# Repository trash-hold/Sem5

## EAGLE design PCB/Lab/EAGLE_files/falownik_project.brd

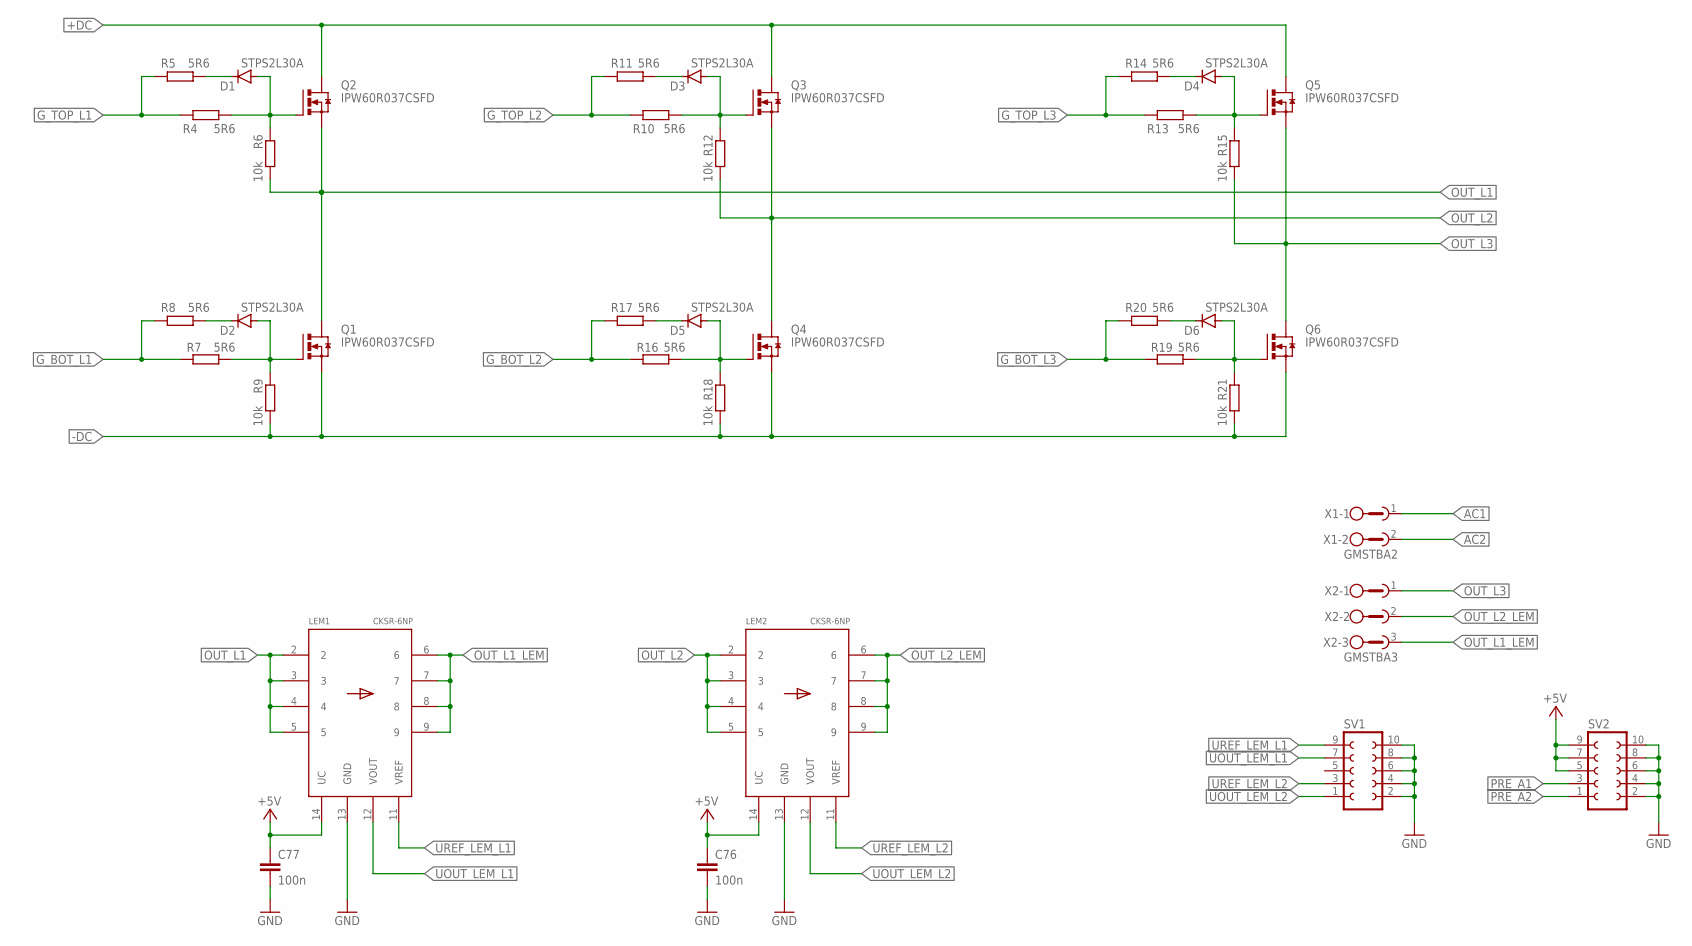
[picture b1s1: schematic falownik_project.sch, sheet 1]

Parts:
C76, C77: 100n; C0805
D1, D2, D3, D4, D5, D6: STPS2L30A; DO214AC
LEM1, LEM2: CKSR-6NP; CKSR
Q1, Q2, Q3, Q4, Q5, Q6: IPW60R037CSFD; TO247BV
R4, R5, R7, R8, R10, R11, R13, R14, R16, R17, R19, R20: 5R6; R0603
R6, R9, R12, R15, R18, R21: 10k; R0603
SV1, SV2: FE05-2
X1: GMSTBA2
X2: GMSTBA3

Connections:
+5V: C76.1, C77.1, LEM1.14 (UC), LEM2.14 (UC), SV2.5, SV2.7, SV2.9; also elsewhere on the board
+DC: Q2.D, Q3.D, Q5.D; also elsewhere on the board
-DC: Q1.S, Q4.S, Q6.S, R9.2, R18.2, R21.2; also elsewhere on the board
AC1: X1.1; also elsewhere on the board
AC2: X1.2; also elsewhere on the board
GND: C76.2, C77.2, LEM1.13 (GND), LEM2.13 (GND), SV1.2, SV1.4, SV1.6, SV1.8, SV1.10, SV2.2, SV2.4, SV2.6, SV2.8, SV2.10; also elsewhere on the board
G_BOT_L1: R7.1, R8.1; also elsewhere on the board
G_BOT_L2: R16.1, R17.1; also elsewhere on the board
G_BOT_L3: R19.1, R20.1; also elsewhere on the board
G_TOP_L1: R4.1, R5.1; also elsewhere on the board
G_TOP_L2: R10.1, R11.1; also elsewhere on the board
G_TOP_L3: R13.1, R14.1; also elsewhere on the board
unnamed: D1.A, Q2.G, R4.2, R6.1
unnamed: D1.C, R5.2
unnamed: D2.A, Q1.G, R7.2, R9.1
unnamed: D2.C, R8.2
unnamed: D3.A, Q3.G, R10.2, R12.1
unnamed: D3.C, R11.2
unnamed: D4.A, Q5.G, R13.2, R15.1
unnamed: D4.C, R14.2
unnamed: D5.A, Q4.G, R16.2, R18.1
unnamed: D5.C, R17.2
unnamed: D6.A, Q6.G, R19.2, R21.1
unnamed: D6.C, R20.2
OUT_L1: LEM1.2, LEM1.3, LEM1.4, LEM1.5, Q1.D, Q2.S, R6.2; also elsewhere on the board
OUT_L1_LEM: LEM1.6, LEM1.7, LEM1.8, LEM1.9, X2.3
OUT_L2: LEM2.2, LEM2.3, LEM2.4, LEM2.5, Q3.S, Q4.D, R12.2; also elsewhere on the board
OUT_L2_LEM: LEM2.6, LEM2.7, LEM2.8, LEM2.9, X2.2
OUT_L3: Q5.S, Q6.D, R15.2, X2.1; also elsewhere on the board
PRE_A1: SV2.3; also elsewhere on the board
PRE_A2: SV2.1; also elsewhere on the board
UOUT_LEM_L1: LEM1.12 (VOUT), SV1.7
UOUT_LEM_L2: LEM2.12 (VOUT), SV1.1
UREF_LEM_L1: LEM1.11 (VREF), SV1.9
UREF_LEM_L2: LEM2.11 (VREF), SV1.3

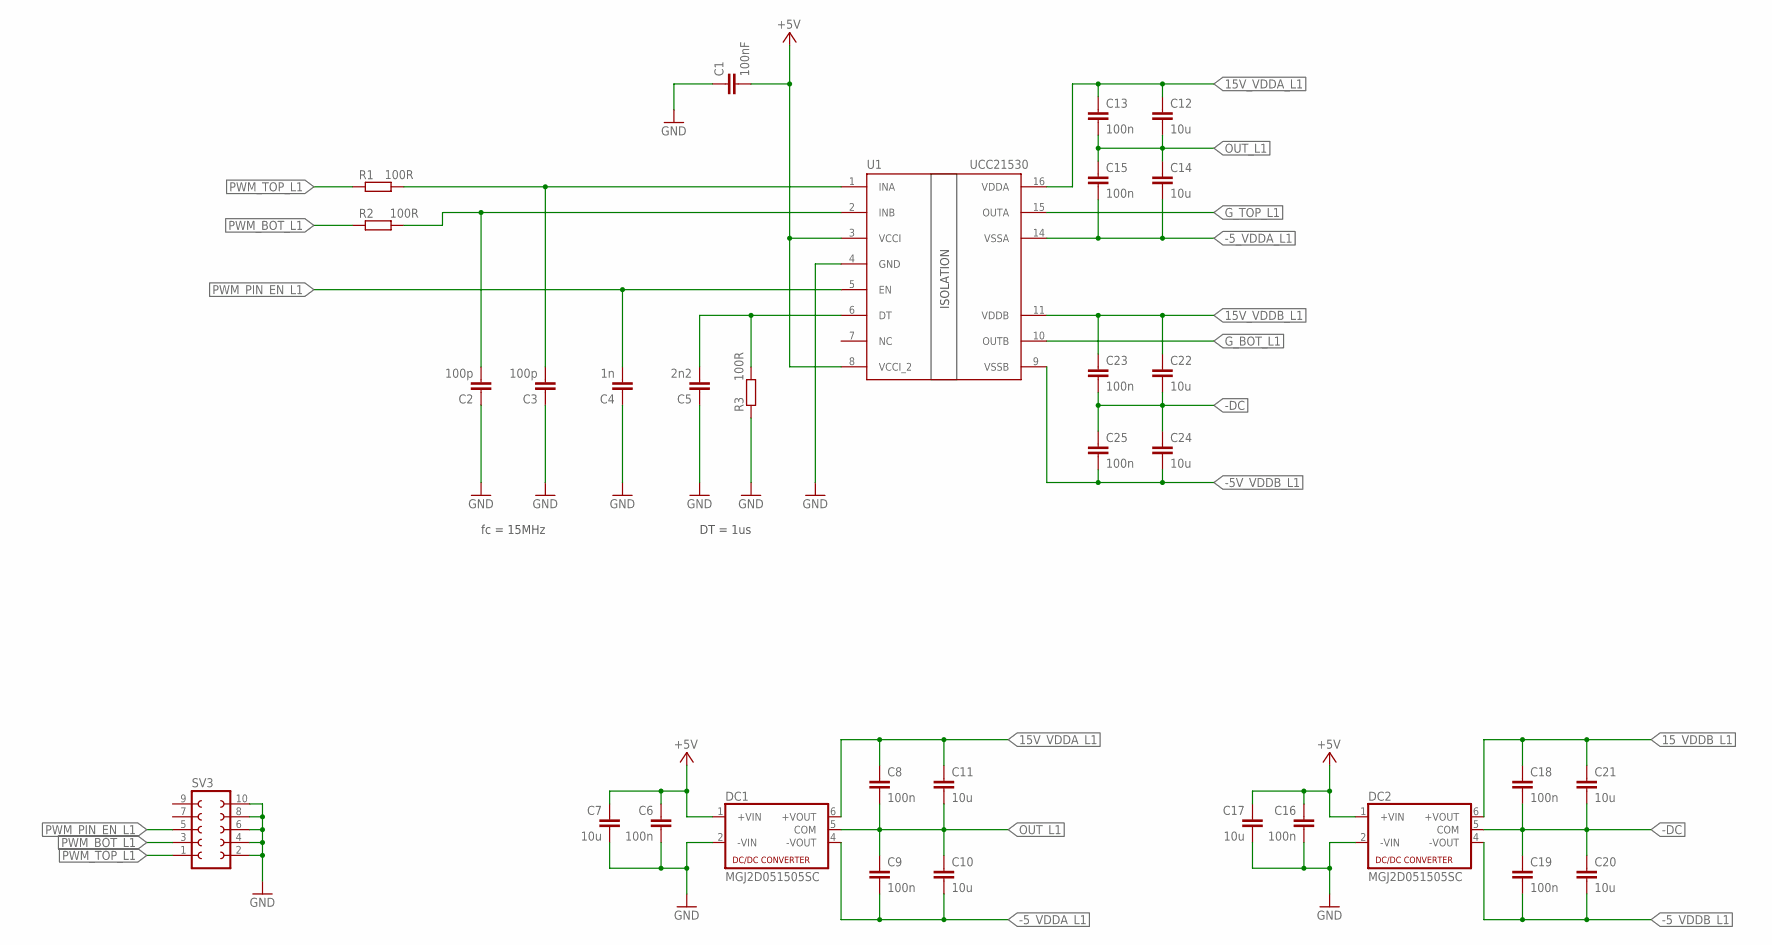
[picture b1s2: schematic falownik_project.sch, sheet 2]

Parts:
C1: 100nF; C0603
C2, C3: 100p; C0603
C4: 1n; C0603
C5: 2n2; C0603
C6, C8, C9, C13, C15, C16, C18, C19, C23, C25: 100n; C0603
C7, C10, C14, C17, C20, C24: 10u; C1206
C11, C12, C21, C22: 10u; C1210
DC1, DC2: MGJ2D051505SC
R1, R2, R3: 100R; R0603
SV3: FE05-2
U1: UCC21530; SOIC-14

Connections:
15V_VDDA_L1: C8.1, C11.1, DC1.6 (+VOUT)
15_VDDB_L1: C18.1, C21.1, DC2.6 (+VOUT)
+5V: C1.2, C6.1, C7.1, C16.1, C17.1, DC1.1 (+VIN), DC2.1 (+VIN), U1.3 (VCCI), U1.8 (VCCI_2); also elsewhere on the board
-5_VDDA_L1: C9.2, C10.2, DC1.4 (-VOUT)
-5_VDDB_L1: C19.2, C20.2, DC2.4 (-VOUT)
-DC: C18.2, C19.1, C20.1, C21.2, C22.2, C23.2, C24.1, C25.1, DC2.5 (COM); also elsewhere on the board
GND: C1.1, C2.1, C3.1, C4.1, C5.1, C6.2, C7.2, C16.2, C17.2, DC1.2 (-VIN), DC2.2 (-VIN), R3.1, SV3.2, SV3.4, SV3.6, SV3.8, SV3.10, U1.4 (GND); also elsewhere on the board
G_BOT_L1: U1.10 (OUTB); also elsewhere on the board
G_TOP_L1: U1.15 (OUTA); also elsewhere on the board
unnamed: C3.2, R1.2, U1.1 (INA)
unnamed: C2.2, R2.2, U1.2 (INB)
unnamed: C5.2, R3.2, U1.6 (DT)
unnamed: C14.2, C15.2, U1.14 (VSSA)
unnamed: C12.1, C13.1, U1.16 (VDDA)
unnamed: C24.2, C25.2, U1.9 (VSSB)
unnamed: C22.1, C23.1, U1.11 (VDDB)
OUT_L1: C8.2, C9.1, C10.1, C11.2, C12.2, C13.2, C14.1, C15.1, DC1.5 (COM); also elsewhere on the board
PWM_BOT_L1: R2.1, SV3.3
PWM_PIN_EN_L1: C4.2, SV3.5, U1.5 (EN)
PWM_TOP_L1: R1.1, SV3.1

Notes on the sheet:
DT = 1us
fc = 15MHz

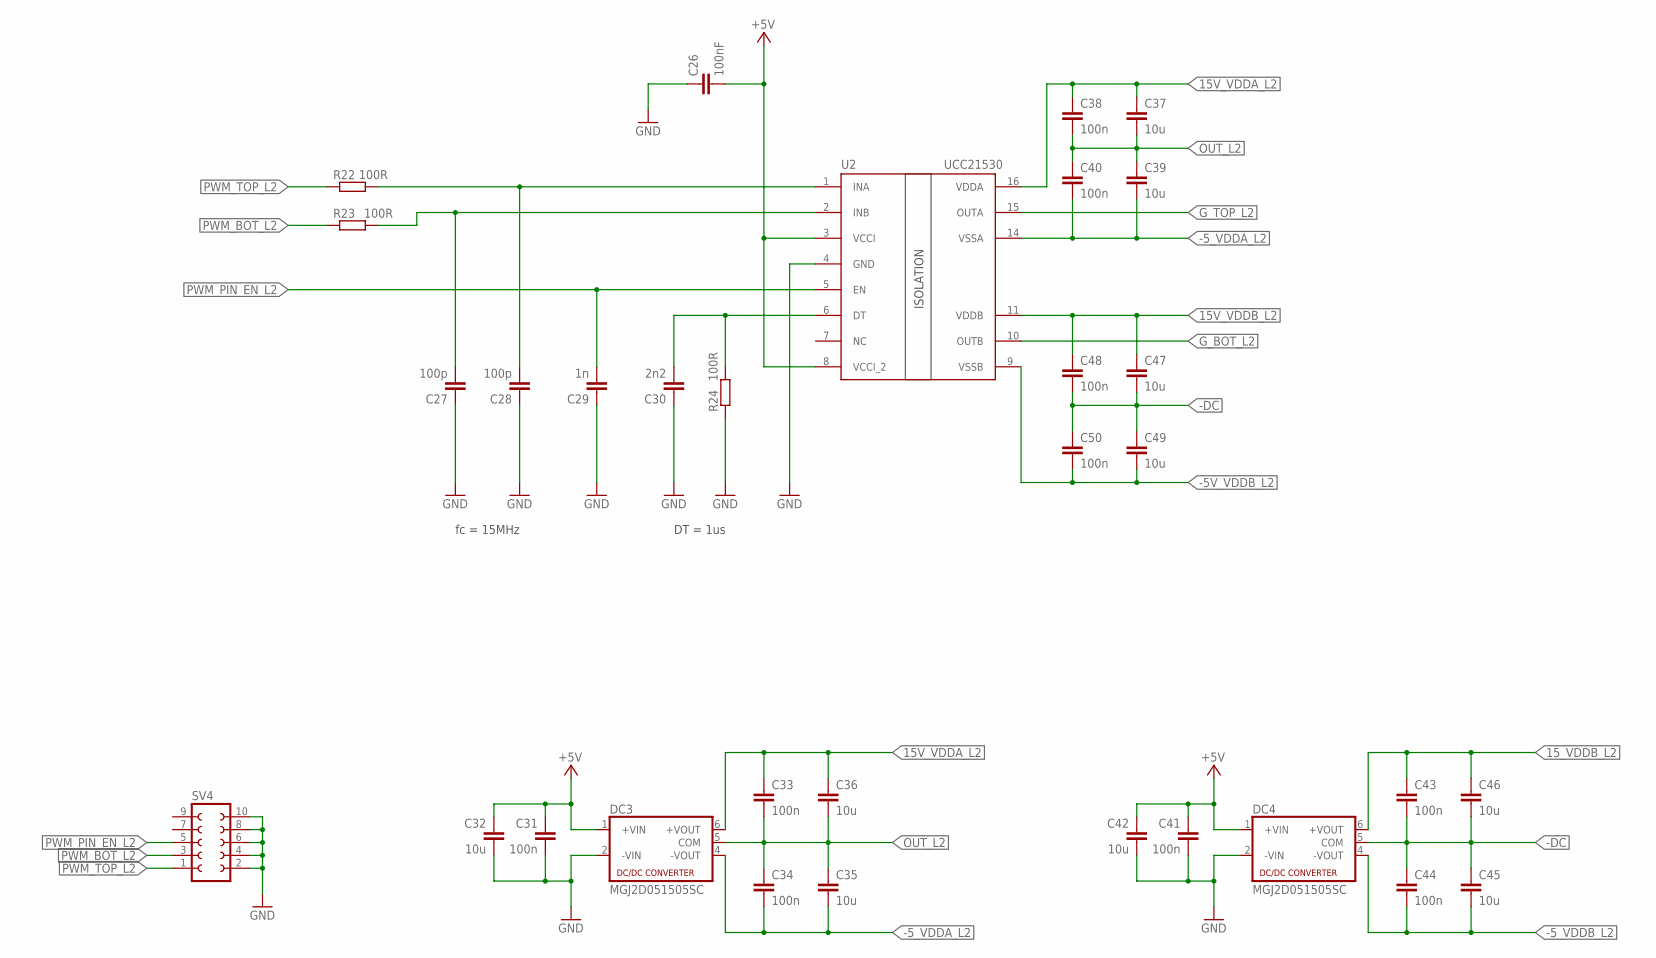
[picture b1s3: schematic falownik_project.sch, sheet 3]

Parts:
C26: 100nF; C0603
C27, C28: 100p; C0603
C29: 1n; C0603
C30: 2n2; C0603
C31, C33, C34, C38, C40, C41, C43, C44, C48, C50: 100n; C0603
C32, C35, C39, C42, C45, C49: 10u; C1206
C36, C37, C46, C47: 10u; C1210
DC3, DC4: MGJ2D051505SC
R22, R23, R24: 100R; R0603
SV4: FE05-2
U2: UCC21530; SOIC-14

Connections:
15V_VDDA_L2: C33.1, C36.1, DC3.6 (+VOUT)
15_VDDB_L2: C43.1, C46.1, DC4.6 (+VOUT)
+5V: C26.2, C31.1, C32.1, C41.1, C42.1, DC3.1 (+VIN), DC4.1 (+VIN), U2.3 (VCCI), U2.8 (VCCI_2); also elsewhere on the board
-5_VDDA_L2: C34.2, C35.2, DC3.4 (-VOUT)
-5_VDDB_L2: C44.2, C45.2, DC4.4 (-VOUT)
-DC: C43.2, C44.1, C45.1, C46.2, C47.2, C48.2, C49.1, C50.1, DC4.5 (COM); also elsewhere on the board
GND: C26.1, C27.1, C28.1, C29.1, C30.1, C31.2, C32.2, C41.2, C42.2, DC3.2 (-VIN), DC4.2 (-VIN), R24.1, SV4.2, SV4.4, SV4.6, SV4.8, SV4.10, U2.4 (GND); also elsewhere on the board
G_BOT_L2: U2.10 (OUTB); also elsewhere on the board
G_TOP_L2: U2.15 (OUTA); also elsewhere on the board
unnamed: C28.2, R22.2, U2.1 (INA)
unnamed: C27.2, R23.2, U2.2 (INB)
unnamed: C30.2, R24.2, U2.6 (DT)
unnamed: C39.2, C40.2, U2.14 (VSSA)
unnamed: C37.1, C38.1, U2.16 (VDDA)
unnamed: C49.2, C50.2, U2.9 (VSSB)
unnamed: C47.1, C48.1, U2.11 (VDDB)
OUT_L2: C33.2, C34.1, C35.1, C36.2, C37.2, C38.2, C39.1, C40.1, DC3.5 (COM); also elsewhere on the board
PWM_BOT_L2: R23.1, SV4.3
PWM_PIN_EN_L2: C29.2, SV4.5, U2.5 (EN)
PWM_TOP_L2: R22.1, SV4.1

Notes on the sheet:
DT = 1us
fc = 15MHz

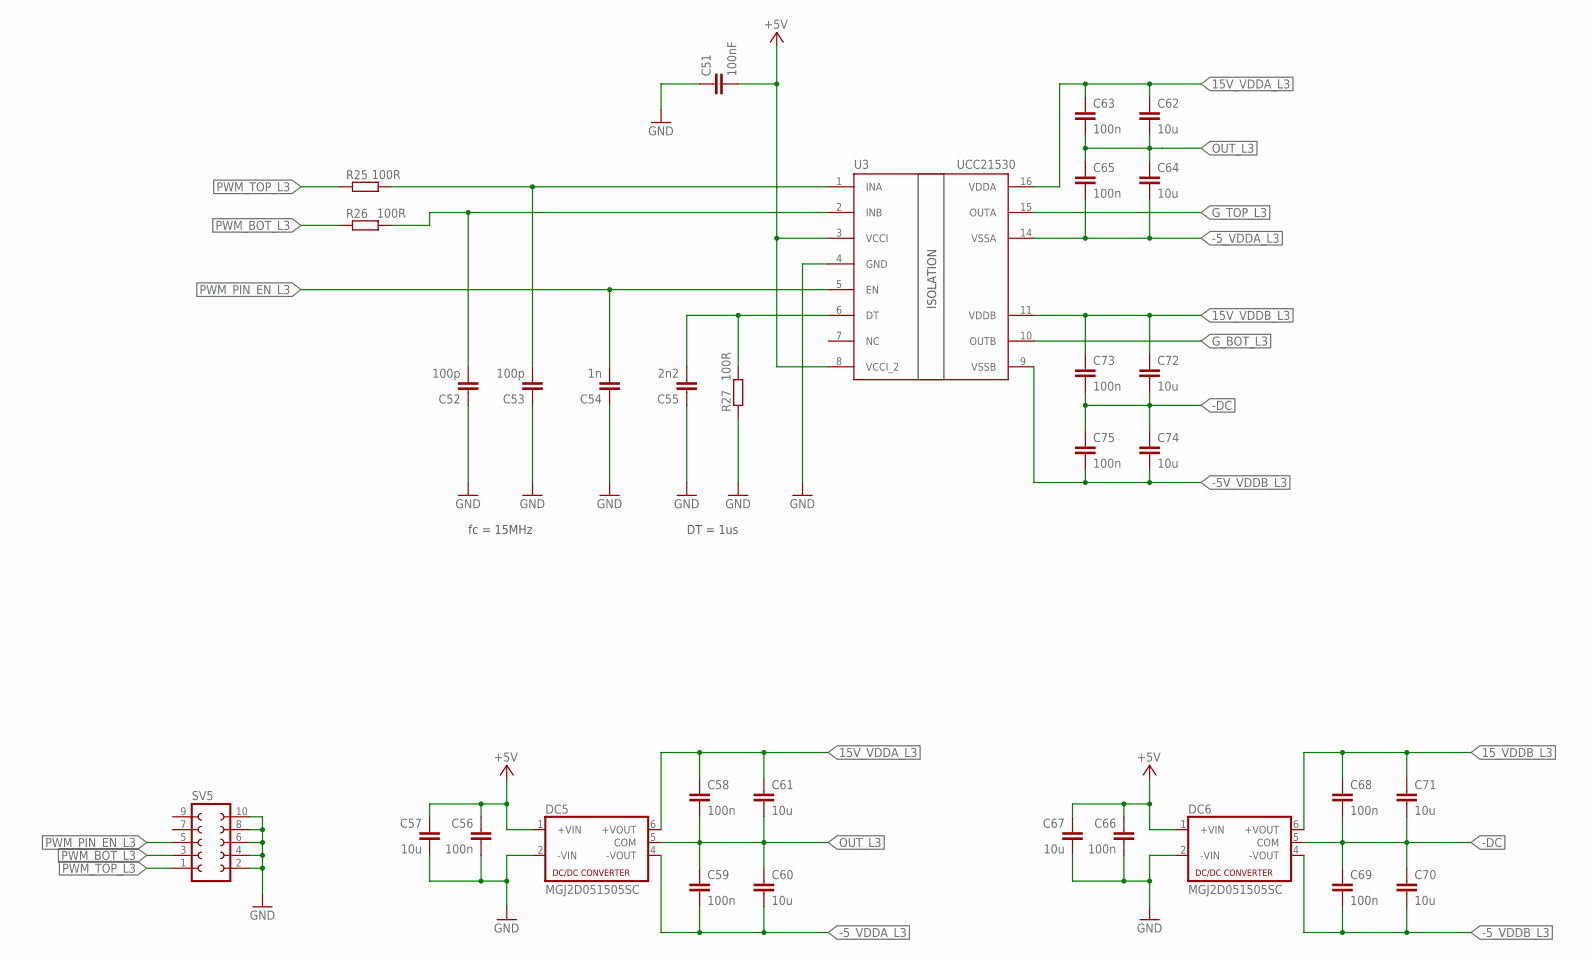
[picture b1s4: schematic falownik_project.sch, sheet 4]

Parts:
C51: 100nF; C0603
C52, C53: 100p; C0603
C54: 1n; C0603
C55: 2n2; C0603
C56, C58, C59, C63, C65, C66, C68, C69, C73, C75: 100n; C0603
C57, C60, C64, C67, C70, C74: 10u; C1206
C61, C62, C71, C72: 10u; C1210
DC5, DC6: MGJ2D051505SC
R25, R26, R27: 100R; R0603
SV5: FE05-2
U3: UCC21530; SOIC-14

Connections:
15V_VDDA_L3: C58.1, C61.1, DC5.6 (+VOUT)
15_VDDB_L3: C68.1, C71.1, DC6.6 (+VOUT)
+5V: C51.2, C56.1, C57.1, C66.1, C67.1, DC5.1 (+VIN), DC6.1 (+VIN), U3.3 (VCCI), U3.8 (VCCI_2); also elsewhere on the board
-5_VDDA_L3: C59.2, C60.2, DC5.4 (-VOUT)
-5_VDDB_L3: C69.2, C70.2, DC6.4 (-VOUT)
-DC: C68.2, C69.1, C70.1, C71.2, C72.2, C73.2, C74.1, C75.1, DC6.5 (COM); also elsewhere on the board
GND: C51.1, C52.1, C53.1, C54.1, C55.1, C56.2, C57.2, C66.2, C67.2, DC5.2 (-VIN), DC6.2 (-VIN), R27.1, SV5.2, SV5.4, SV5.6, SV5.8, SV5.10, U3.4 (GND); also elsewhere on the board
G_BOT_L3: U3.10 (OUTB); also elsewhere on the board
G_TOP_L3: U3.15 (OUTA); also elsewhere on the board
unnamed: C53.2, R25.2, U3.1 (INA)
unnamed: C52.2, R26.2, U3.2 (INB)
unnamed: C55.2, R27.2, U3.6 (DT)
unnamed: C64.2, C65.2, U3.14 (VSSA)
unnamed: C62.1, C63.1, U3.16 (VDDA)
unnamed: C74.2, C75.2, U3.9 (VSSB)
unnamed: C72.1, C73.1, U3.11 (VDDB)
OUT_L3: C58.2, C59.1, C60.1, C61.2, C62.2, C63.2, C64.1, C65.1, DC5.5 (COM); also elsewhere on the board
PWM_BOT_L3: R26.1, SV5.3
PWM_PIN_EN_L3: C54.2, SV5.5, U3.5 (EN)
PWM_TOP_L3: R25.1, SV5.1

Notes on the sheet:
DT = 1us
fc = 15MHz

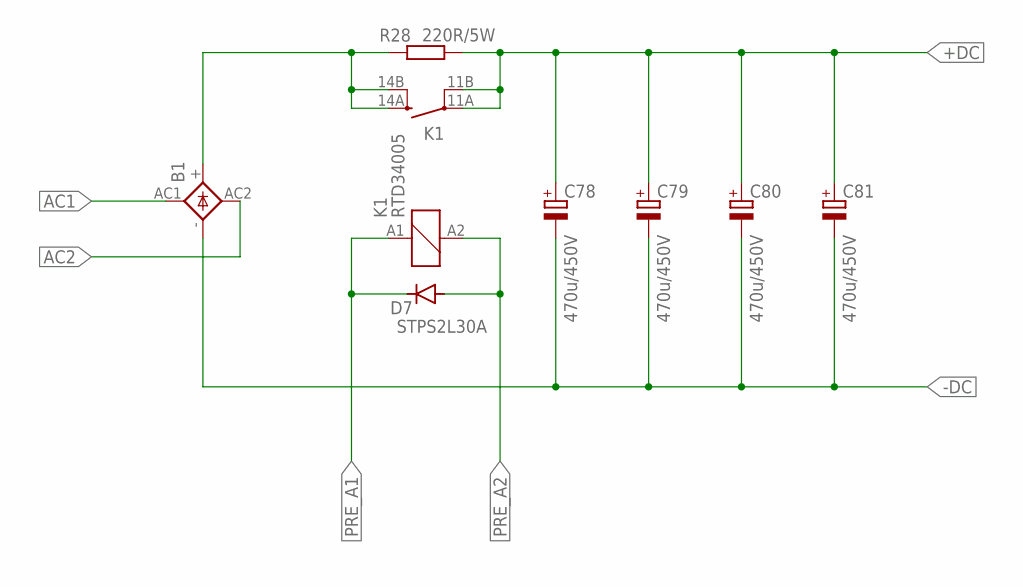
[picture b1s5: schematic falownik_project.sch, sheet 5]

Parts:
B1: GBPC80X
C78, C79, C80, C81: 470u/450V; EB30D
D7: STPS2L30A; DO214AC
K1: RTD34005; RT-N/O16A5
R28: 220R/5W; VTA52

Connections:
+DC: C78.+, C79.+, C80.+, C81.+, K1.11A (PA), K1.11B (PB), R28.2; also elsewhere on the board
-DC: B1.-, C78.-, C79.-, C80.-, C81.-; also elsewhere on the board
AC1: B1.AC1; also elsewhere on the board
AC2: B1.AC2; also elsewhere on the board
unnamed: B1.+, K1.14A (SA), K1.14B (SB), R28.1
PRE_A1: D7.C, K1.A1 (1); also elsewhere on the board
PRE_A2: D7.A, K1.A2 (2); also elsewhere on the board

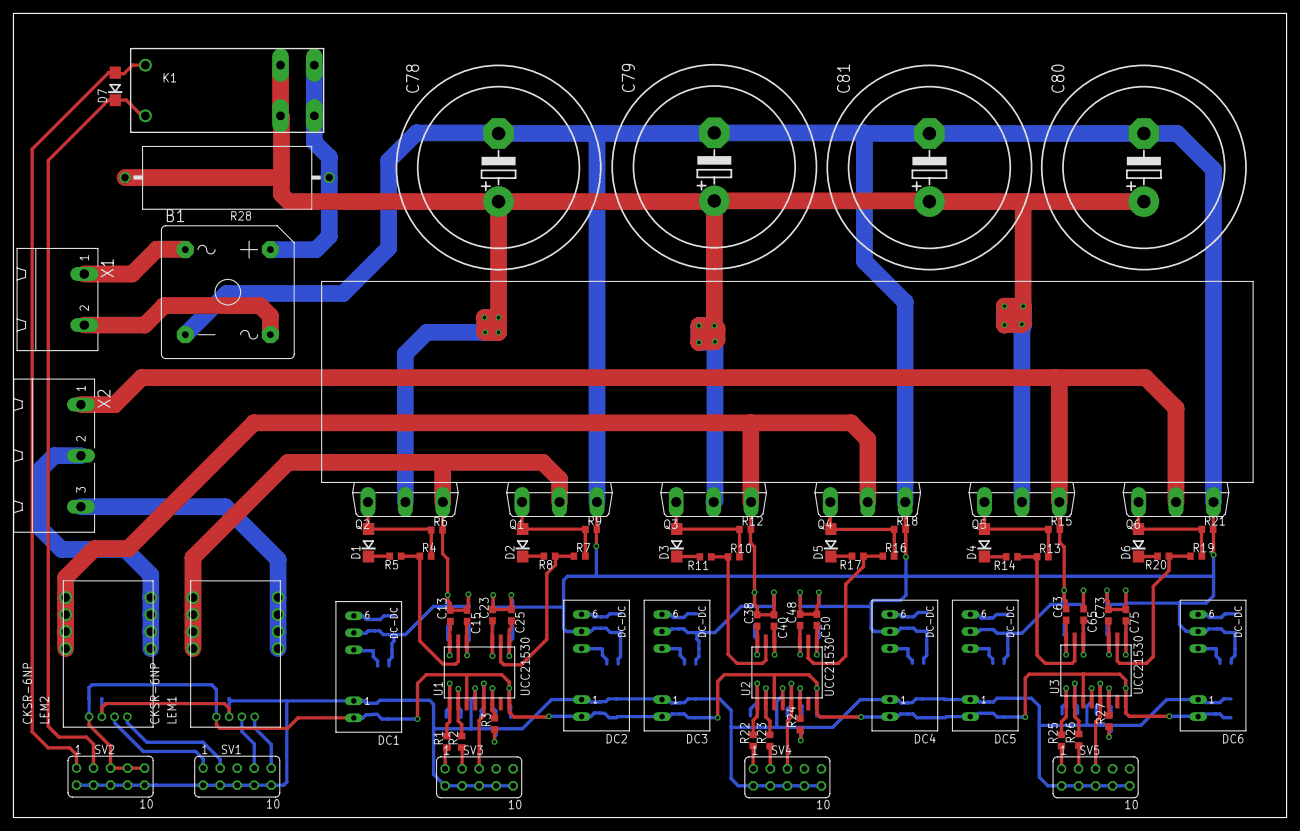
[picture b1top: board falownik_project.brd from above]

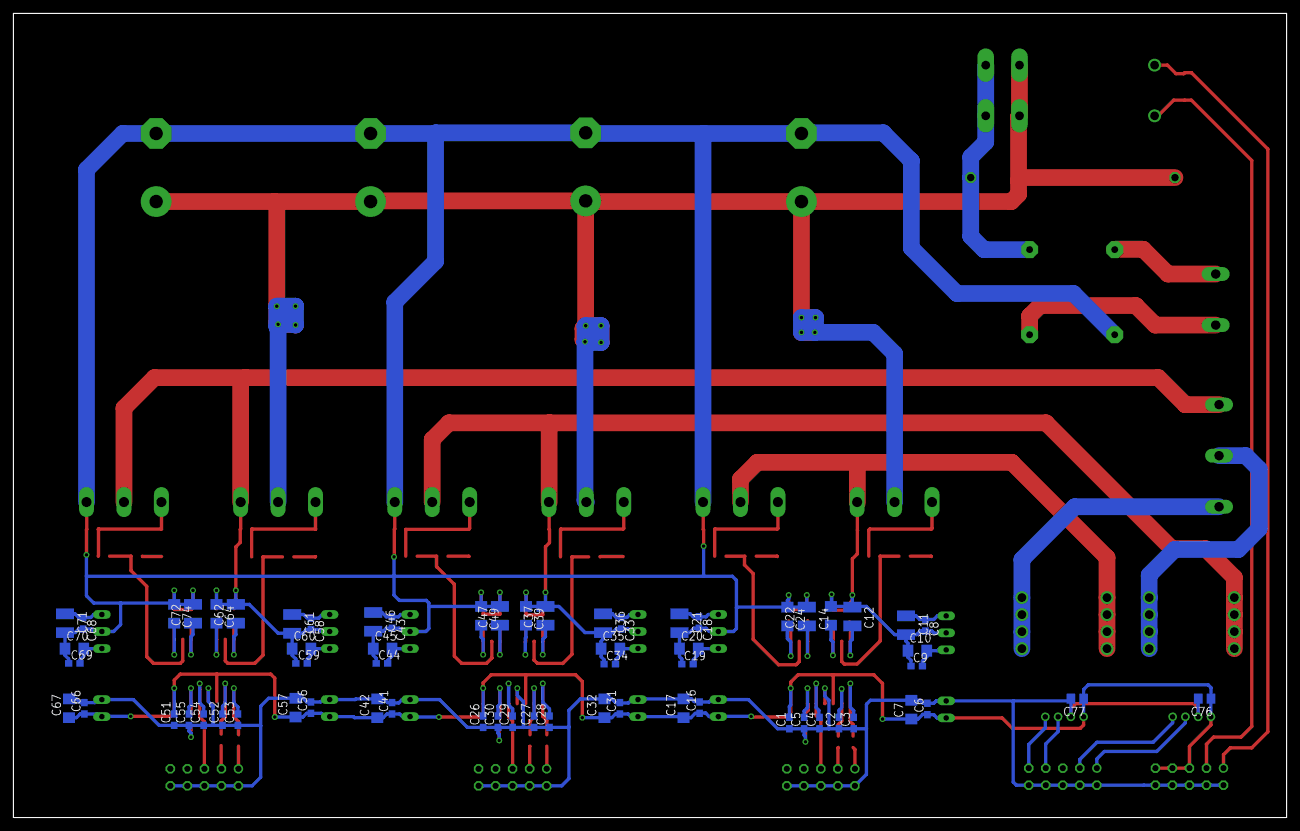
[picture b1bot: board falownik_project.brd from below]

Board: 2 copper layers, 190.0 x 120.0 mm, 142 parts (65 on the bottom side), 78 nets.

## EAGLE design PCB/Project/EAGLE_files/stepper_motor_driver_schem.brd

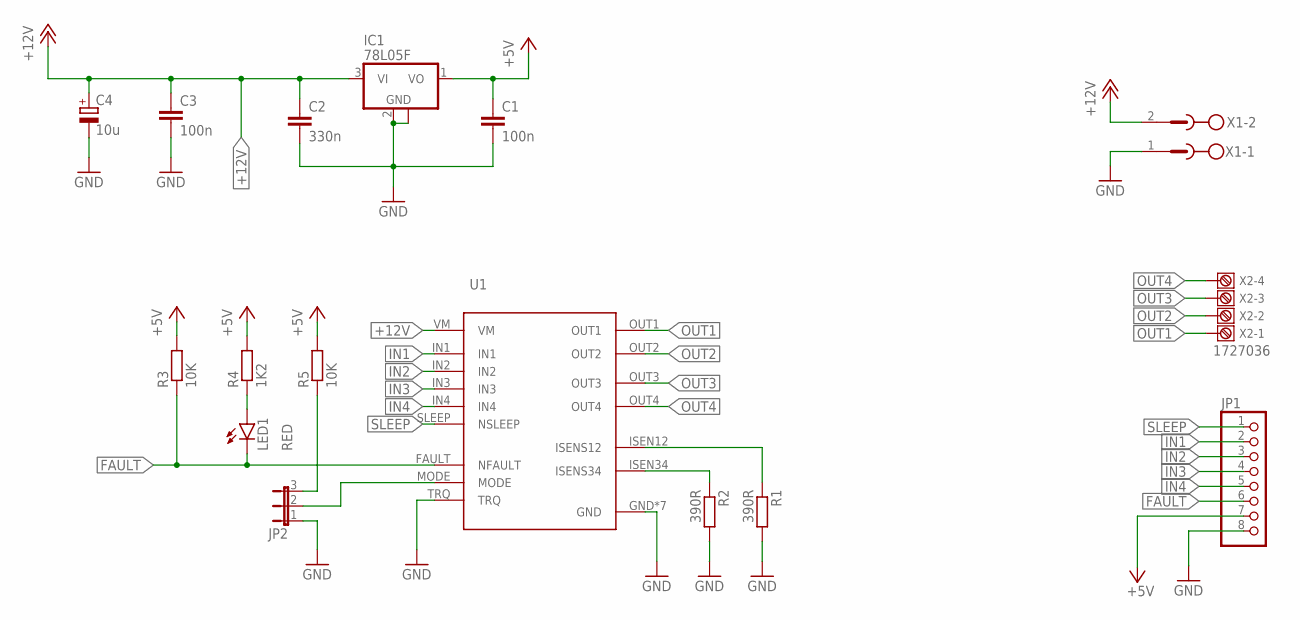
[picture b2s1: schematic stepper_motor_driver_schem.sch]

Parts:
C1, C3: 100n; C0402
C2: 330n; C0402
C4: 10u; E2-5
IC1: 78L05F; SOT89
JP1: PINHD-1X8; 1X08
JP2: JP2E; JP2
LED1: RED; CHIP-LED0603
R1, R2: 390R; R1206
R3, R5: 10K; R0603
R4: 1K2; R0603
U1: DRV8847RTER
X1: MSTBV2
X2: 1727036

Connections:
+5V: C1.1, IC1.1 (VO), JP1.7, R3.2, R4.2, R5.2
+12V: C2.1, C3.1, C4.+, IC1.3 (VI), U1.VM, X1.2
FAULT: JP1.6, LED1.C, R3.1, U1.FAULT (NFAULT)
GND: C1.2, C2.2, C3.2, C4.-, IC1.2 (GND), IC1.2@1 (GND), JP1.8, JP2.1, R1.2, R2.2, U1.GND, U1.T1 (GND), U1.T2 (GND), U1.T3 (GND), U1.T4 (GND), U1.T5 (GND), U1.THERMAL_PAD (GND), U1.TRQ, X1.1
IN1: JP1.2, U1.IN1
IN2: JP1.3, U1.IN2
IN3: JP1.4, U1.IN3
IN4: JP1.5, U1.IN4
unnamed: R2.1, U1.ISEN34 (ISENS34)
unnamed: R1.1, U1.ISEN12 (ISENS12)
unnamed: LED1.A, R4.1
unnamed: JP2.2, U1.MODE
unnamed: JP2.3, R5.1
OUT1: U1.OUT1, X2.1
OUT2: U1.OUT2, X2.2
OUT3: U1.OUT3, X2.3
OUT4: U1.OUT4, X2.4
SLEEP: JP1.1, U1.SLEEP (NSLEEP)

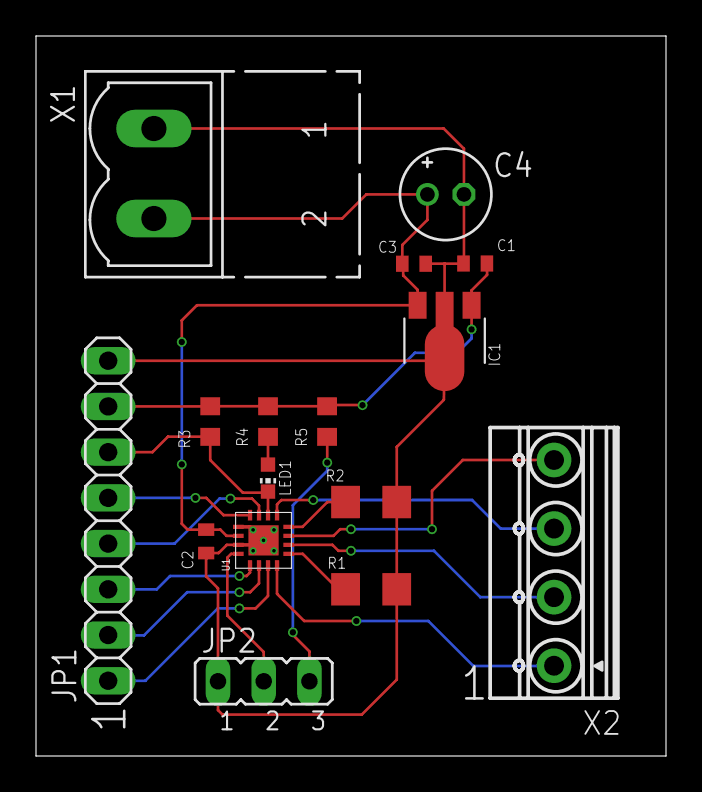
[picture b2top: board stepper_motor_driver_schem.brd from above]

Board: 2 copper layers, 35.0 x 40.0 mm, 16 parts (0 on the bottom side), 18 nets.

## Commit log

2023-11-14 Init
2023-11-14 Lab1+2
